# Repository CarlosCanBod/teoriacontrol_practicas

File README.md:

# teoriacontrol_practicas
Codigos y archivos de practicas de teoria de control

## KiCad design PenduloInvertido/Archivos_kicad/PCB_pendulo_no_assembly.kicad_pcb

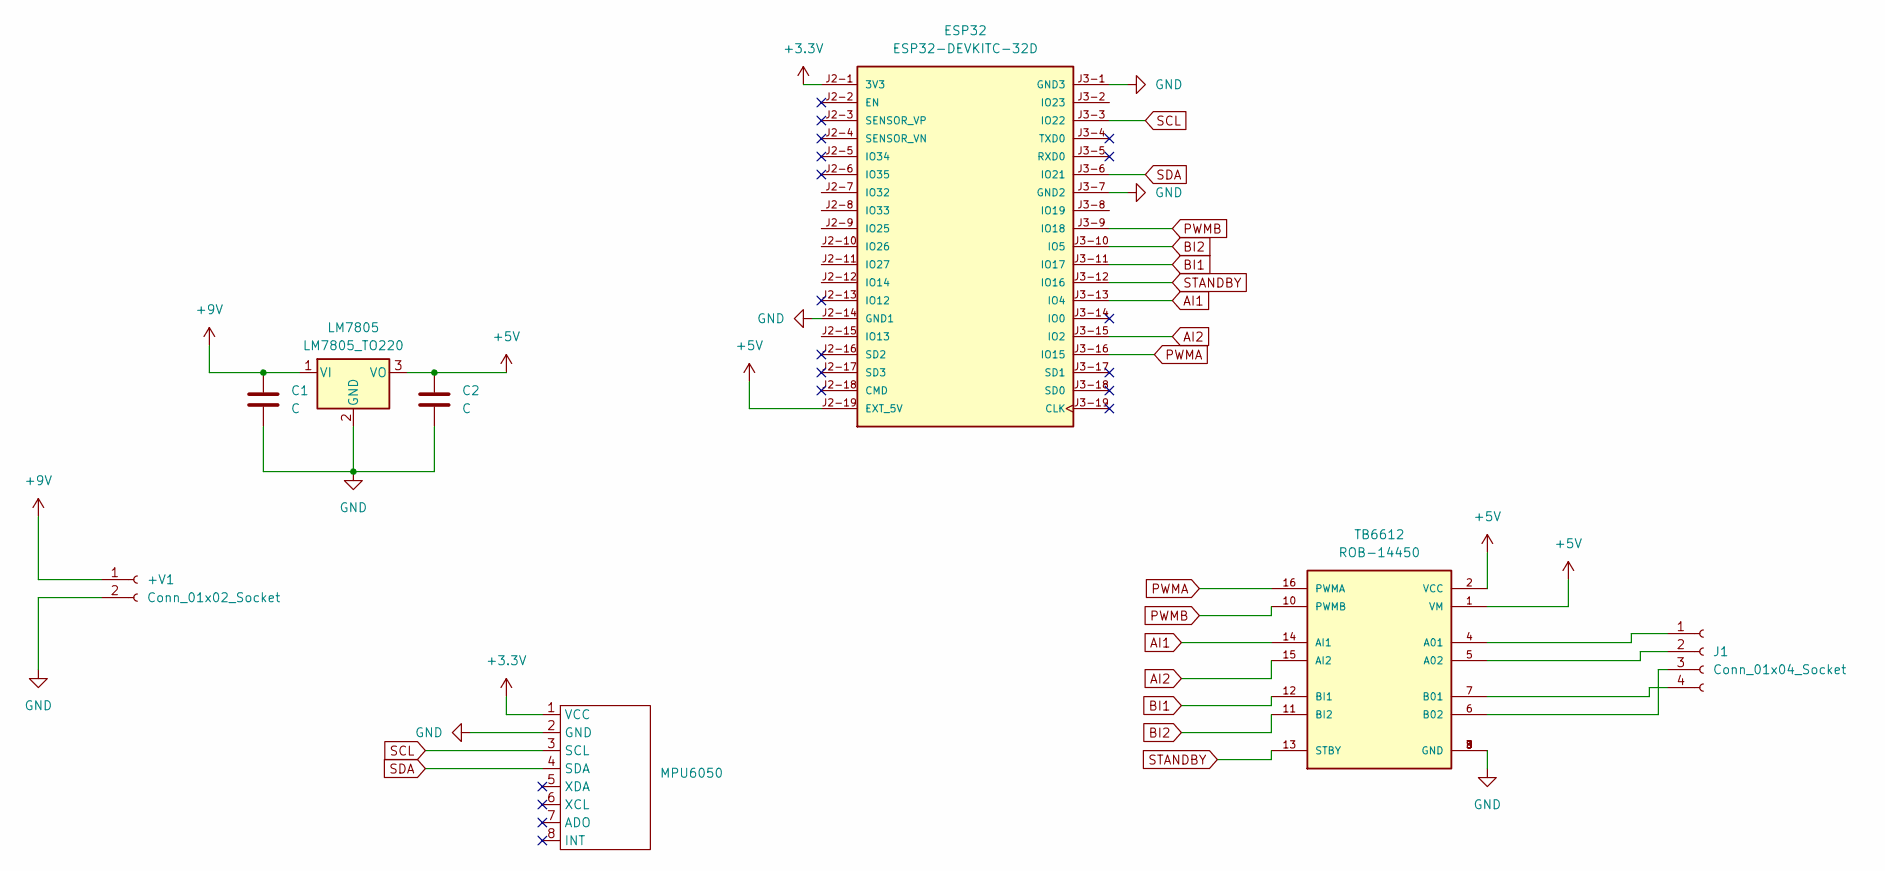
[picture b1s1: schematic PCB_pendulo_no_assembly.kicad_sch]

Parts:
+V1: Conn_01x02_Socket; PinHeader_1x02_P2.54mm_Vertical
C1, C2: C; C_Disc_D3.0mm_W2.0mm_P2.50mm
ESP32: ESP32-DEVKITC-32D; MODULE_ESP32-DEVKITC-32D; PARTREV V4
J1: Conn_01x04_Socket; PinSocket_1x04_P2.54mm_Vertical
LM7805: LM7805_TO220; TO-220-3_Vertical
MPU6050: MPU_6050_montadito
TB6612: ROB-14450; MODULE_ROB-14450; PARTREV 11-13-17

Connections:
+3.3V: ESP32.J2-1 (3V3), MPU6050.1 (VCC)
+5V: C2.1, ESP32.J2-19 (EXT_5V), LM7805.3 (VO), TB6612.1 (VM), TB6612.2 (VCC)
+9V: +V1.1, C1.1, LM7805.1 (VI)
AI1: ESP32.J3-13 (IO4), TB6612.14 (AI1)
AI2: ESP32.J3-15 (IO2), TB6612.15 (AI2)
BI1: ESP32.J3-11 (IO17), TB6612.12 (BI1)
BI2: ESP32.J3-10 (IO5), TB6612.11 (BI2)
GND: +V1.2, C1.2, C2.2, ESP32.J2-14 (GND1), ESP32.J3-1 (GND3), ESP32.J3-7 (GND2), LM7805.2 (GND), MPU6050.2 (GND), TB6612.3 (GND), TB6612.8 (GND), TB6612.9 (GND)
unnamed: J1.1, TB6612.4 (A01)
unnamed: J1.2, TB6612.5 (A02)
unnamed: J1.3, TB6612.6 (B02)
unnamed: J1.4, TB6612.7 (B01)
PWMA: ESP32.J3-16 (IO15), TB6612.16 (PWMA)
PWMB: ESP32.J3-9 (IO18), TB6612.10 (PWMB)
SCL: ESP32.J3-3 (IO22), MPU6050.3 (SCL)
SDA: ESP32.J3-6 (IO21), MPU6050.4 (SDA)
STANDBY: ESP32.J3-12 (IO16), TB6612.13 (STBY)

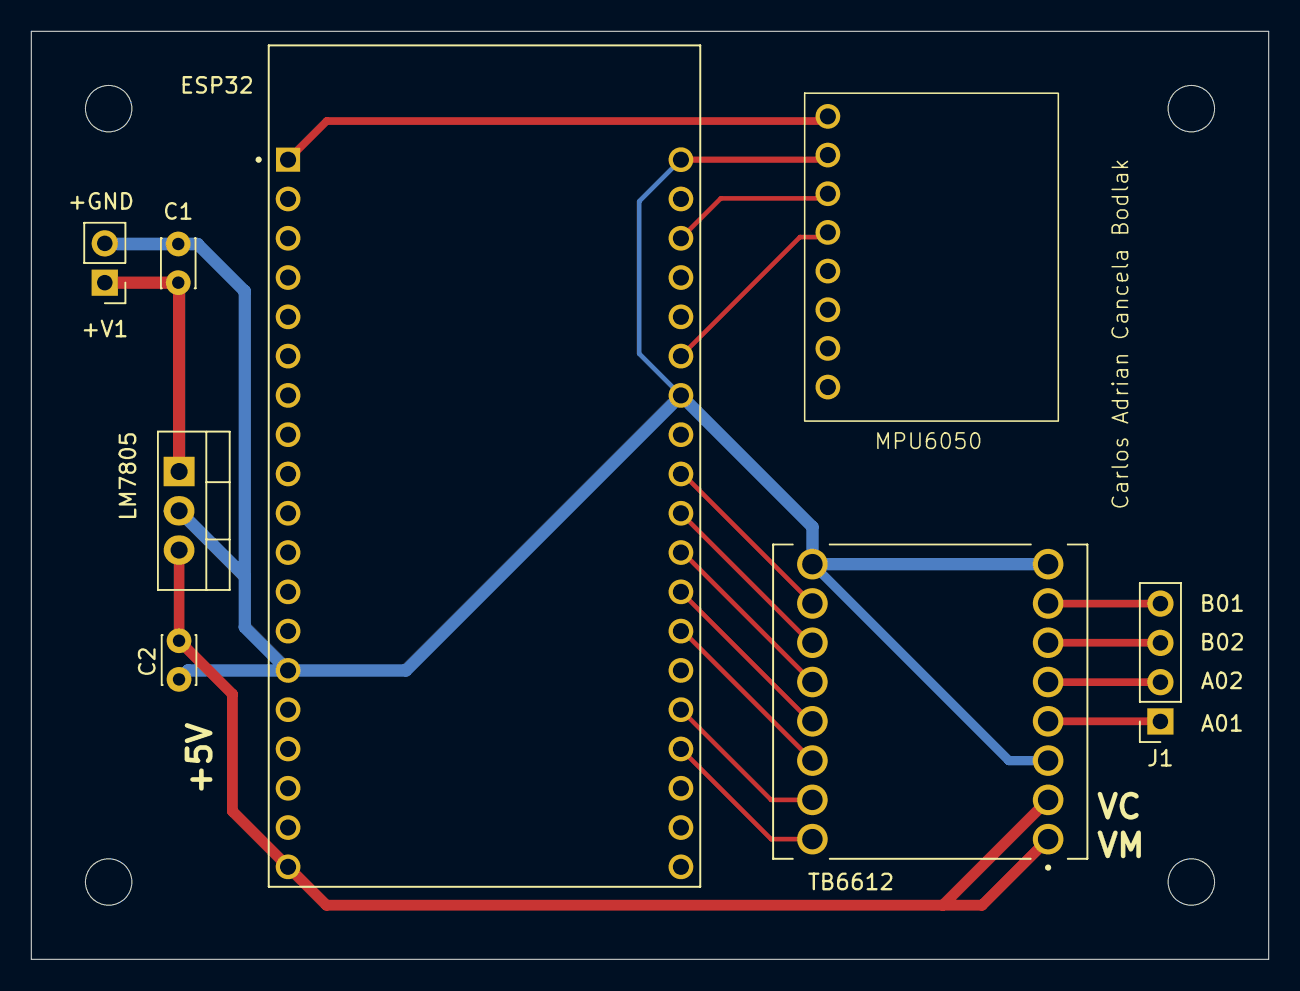
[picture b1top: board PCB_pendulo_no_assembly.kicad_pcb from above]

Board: 2 copper layers, 80.0 x 60.0 mm, 8 parts (0 on the bottom side), 17 nets.
